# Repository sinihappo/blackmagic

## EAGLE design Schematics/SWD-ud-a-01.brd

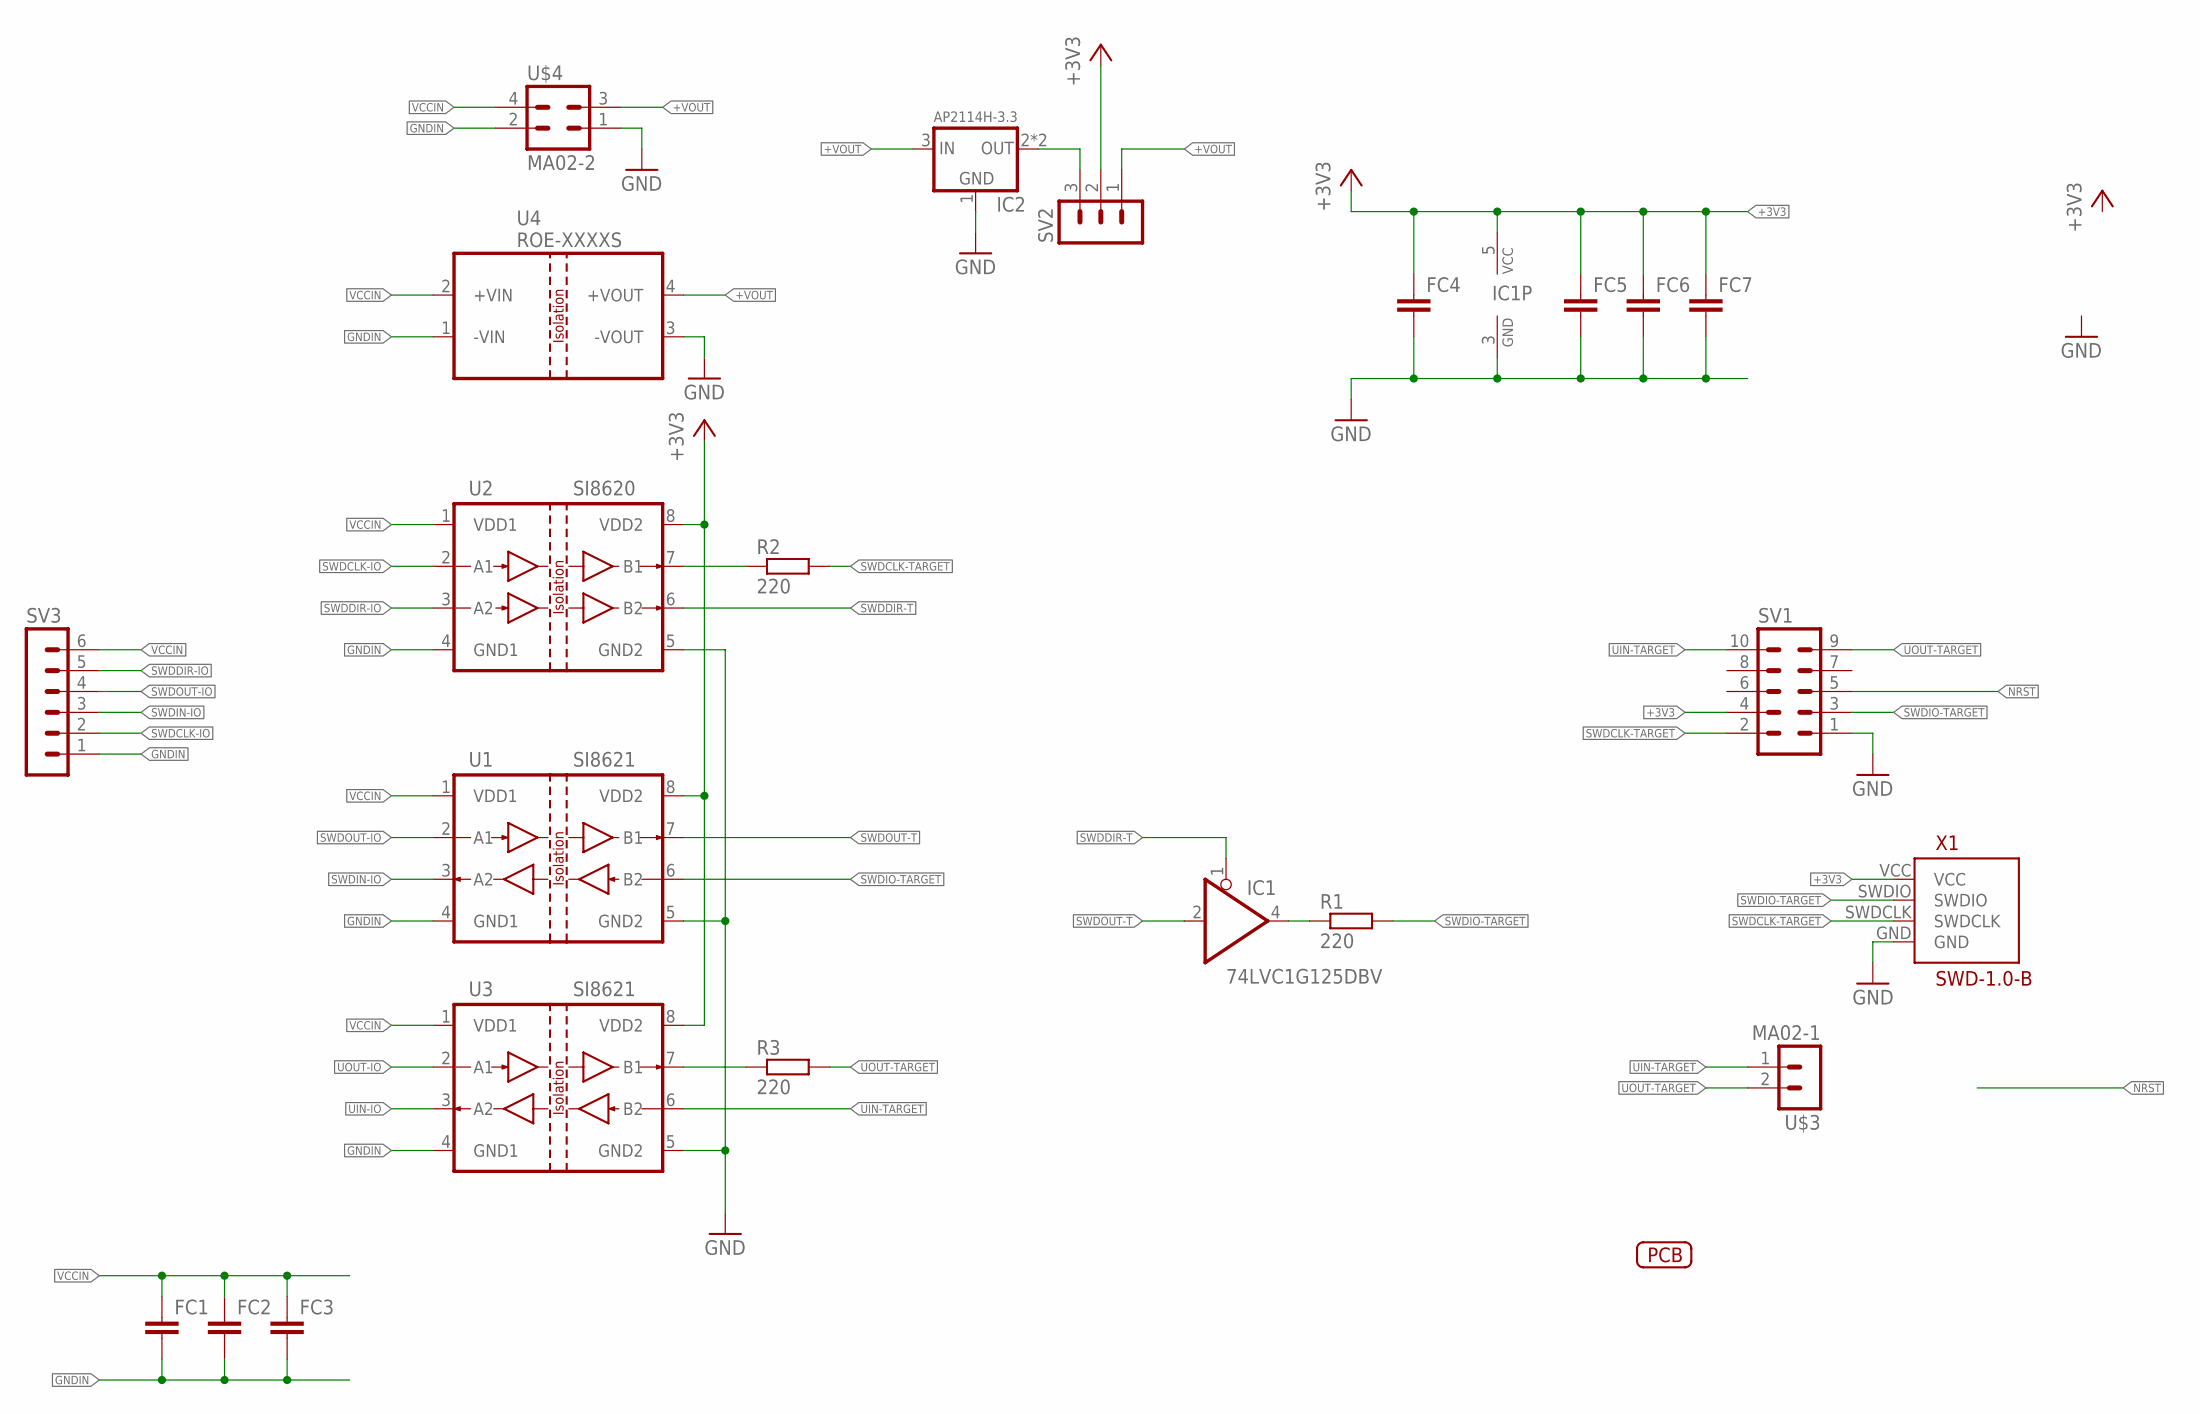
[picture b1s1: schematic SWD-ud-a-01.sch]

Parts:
FC1, FC2, FC3, FC4, FC5, FC6, FC7: C-EUC0805; C0805
IC1: 74LVC1G125DBV; SOT23-5
IC2: AP2114H-3.3; SOT223; PARTNO AP2114H-3.3TRG1DICT-ND
R1, R2, R3: 220; R0603
SV1: MA05-2
SV2: MA03-1
SV3: MA06-1
U1, U3: SI8621; SOIC-8
U2: SI8620; SOIC-8
U4: ROE-XXXXS; ROE-SIP-4
U$2: ENCLOSURE-CN-60X54
U$3: MA02-1
U$4: MA02-2
X1: SWD-1.0-B

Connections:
+3V3: FC4.1, FC5.1, FC6.1, FC7.1, IC1.5 (VCC), SV1.4, SV2.2, U1.8 (VDD2), U2.8 (VDD2), U3.8 (VDD2), X1.VCC
+VOUT: IC2.3 (IN), SV2.1, U4.4 (+VOUT), U$4.3
GND: FC4.2, FC5.2, FC6.2, FC7.2, IC1.3 (GND), IC2.1 (GND), SV1.1, U1.5 (GND2), U2.5 (GND2), U3.5 (GND2), U4.3 (-VOUT), U$4.1, X1.GND
GNDIN: FC1.2, FC2.2, FC3.2, SV3.1, U1.4 (GND1), U2.4 (GND1), U3.4 (GND1), U4.1 (-VIN), U$4.2
unnamed: IC1.4 (O), R1.1
unnamed: R2.1, U2.7 (B1)
unnamed: R3.1, U3.7 (B1)
unnamed: IC2.2 (OUT), IC2.TAB (OUT), SV2.3
NRST: SV1.5
SWDCLK-IO: SV3.2, U2.2 (A1)
SWDCLK-TARGET: R2.2, SV1.2, X1.SWDCLK
SWDDIR-IO: SV3.5, U2.3 (A2)
SWDDIR-T: IC1.1 (OE), U2.6 (B2)
SWDIN-IO: SV3.3, U1.3 (A2)
SWDIO-TARGET: R1.2, SV1.3, U1.6 (B2), X1.SWDIO
SWDOUT-IO: SV3.4, U1.2 (A1)
SWDOUT-T: IC1.2 (I), U1.7 (B1)
UIN-IO: U3.3 (A2)
UIN-TARGET: SV1.10, U3.6 (B2), U$3.1
UOUT-IO: U3.2 (A1)
UOUT-TARGET: R3.2, SV1.9, U$3.2
VCCIN: FC1.1, FC2.1, FC3.1, SV3.6, U1.1 (VDD1), U2.1 (VDD1), U3.1 (VDD1), U4.2 (+VIN), U$4.4

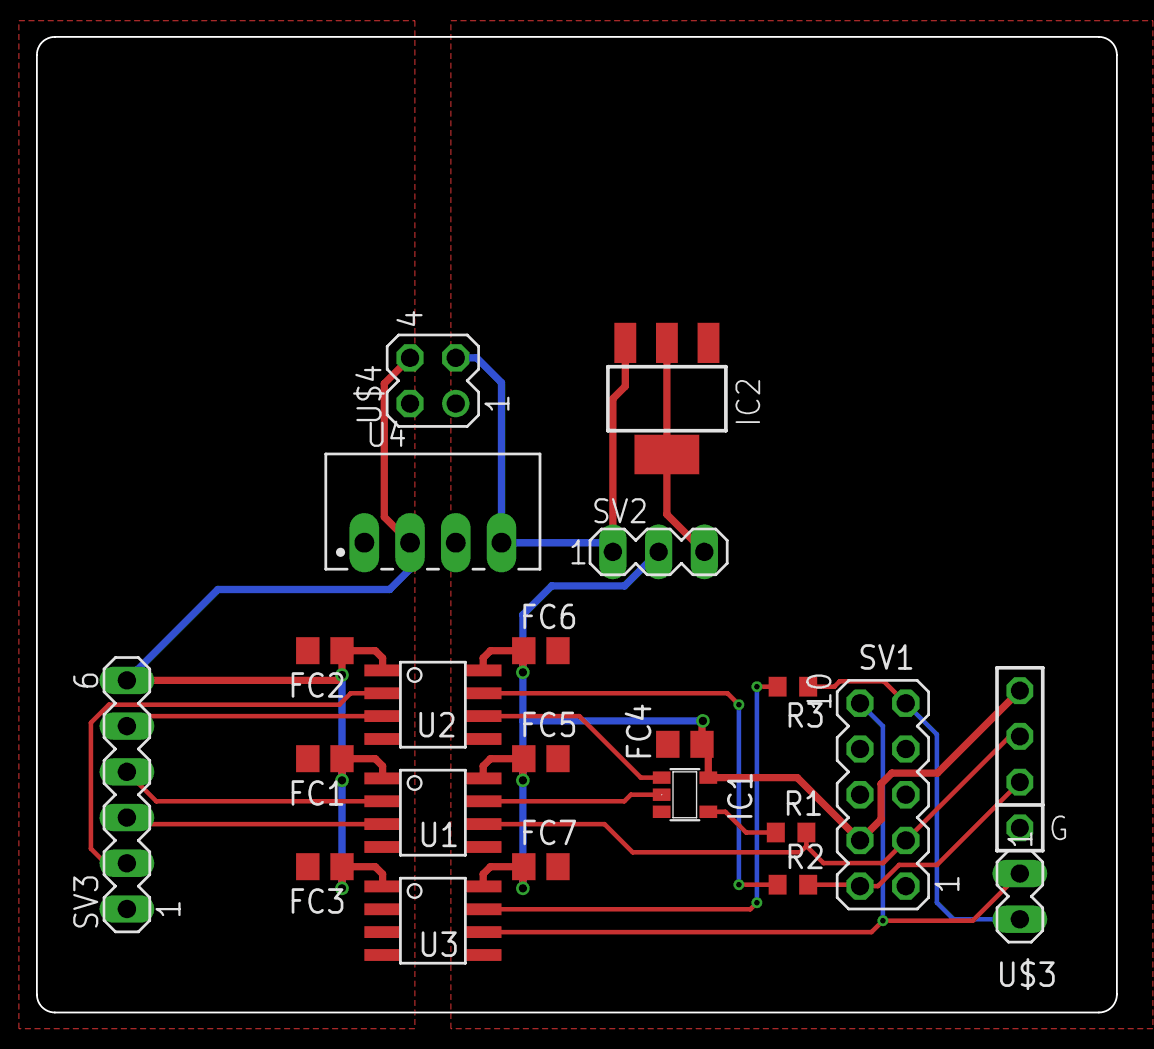
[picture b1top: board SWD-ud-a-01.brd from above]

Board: 2 copper layers, 60.0 x 54.2 mm, 23 parts (0 on the bottom side), 19 nets.

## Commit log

2018-07-28 Delay test.
2019-07-31 stlink-ud for unidirectional digital isolators.
2019-09-01 Schematics
